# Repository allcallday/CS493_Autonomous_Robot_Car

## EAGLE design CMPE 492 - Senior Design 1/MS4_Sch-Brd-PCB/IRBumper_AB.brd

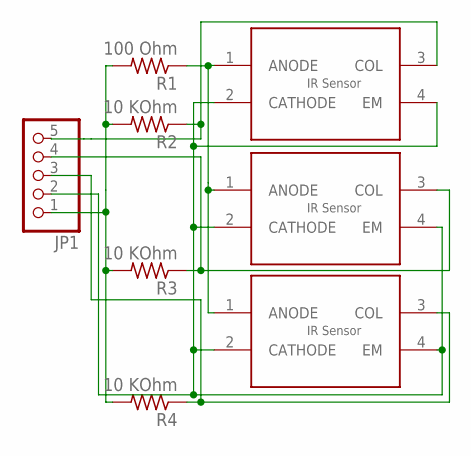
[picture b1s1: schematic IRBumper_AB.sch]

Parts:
JP1: PINHD-1X5; 1X05
R1: 100 Ohm; M0805
R2, R3, R4: 10 KOhm; M0805
U$1, U$2, U$3: QRE1113GR; 4-SMD

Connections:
GND: JP1.2, U$1.2 (CATHODE), U$1.4 (EM), U$2.2 (CATHODE), U$2.4 (EM), U$3.2 (CATHODE), U$3.4 (EM)
unnamed: R1.1, U$1.1 (ANODE), U$2.1 (ANODE), U$3.1 (ANODE)
unnamed: JP1.5, R2.1, U$2.3 (COL)
unnamed: JP1.4, R3.1, U$1.3 (COL)
unnamed: JP1.3, R4.1, U$3.3 (COL)
VDD_5: JP1.1, R1.2, R2.2, R3.2, R4.2

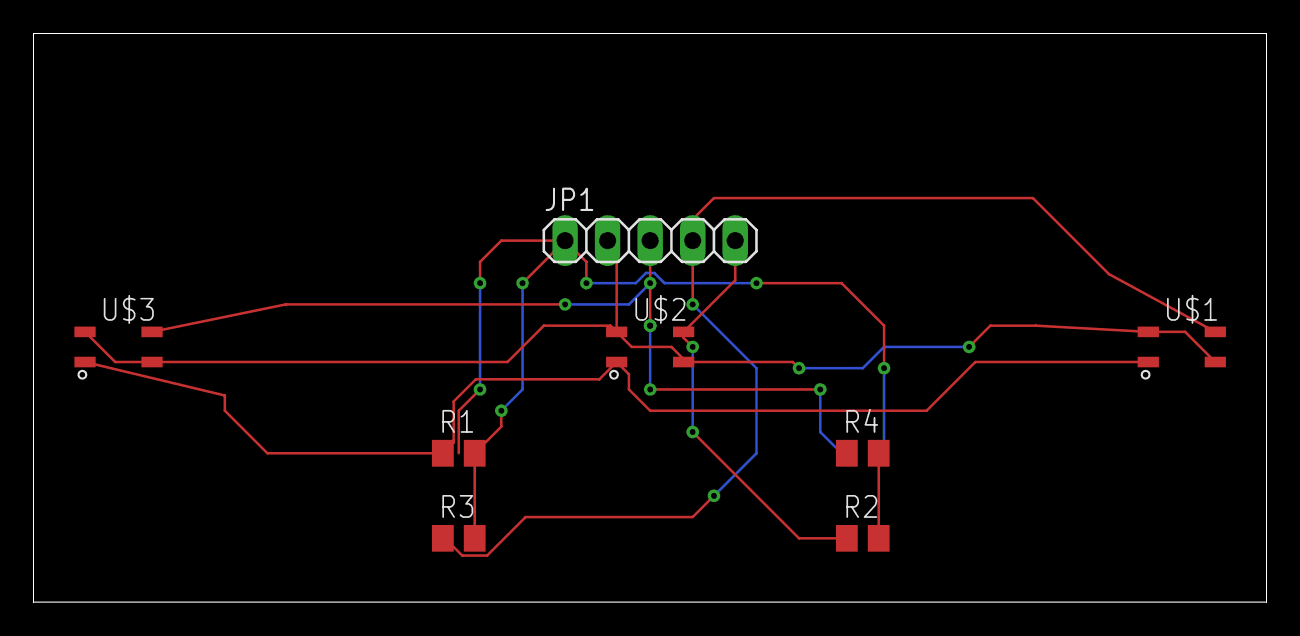
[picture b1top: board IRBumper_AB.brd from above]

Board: 2 copper layers, 73.6 x 34.0 mm, 8 parts (0 on the bottom side), 6 nets.

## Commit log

2021-09-21 Moving project files from Google Drive to GitHub
